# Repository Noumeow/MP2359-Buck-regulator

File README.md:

# MP2359-Buck-regulator
This is the first buck regulator I designed following the datasheet as correctly as I could without following any tutorial or anything
Here the voltage can be regulated more efficiently and 12V is stepped down to 3.3V
The enable pin has to have less than 6V for turning the chip on
The feedback resistors help in controlling the output to 3.3V
The A03401A p channel MOSFET works as a reverse polarity protection and better than the diode 1N4007 since the voltage drop in MOSFET is around 50-100mV while for the diode it is almost 0.7V.So the MOSFET is basically superior in terms of voltage drop,efficiency and heat dissipation

# Known Limitations and Future Improvements
The SW loop path with catch diode,inductor and capacitor needs to be as small as possible and clustered together.Even a few mm increase in trace introduce inductance causing voltage spike,electromagnetic interference and efficiency loss which needs to be improved in this design

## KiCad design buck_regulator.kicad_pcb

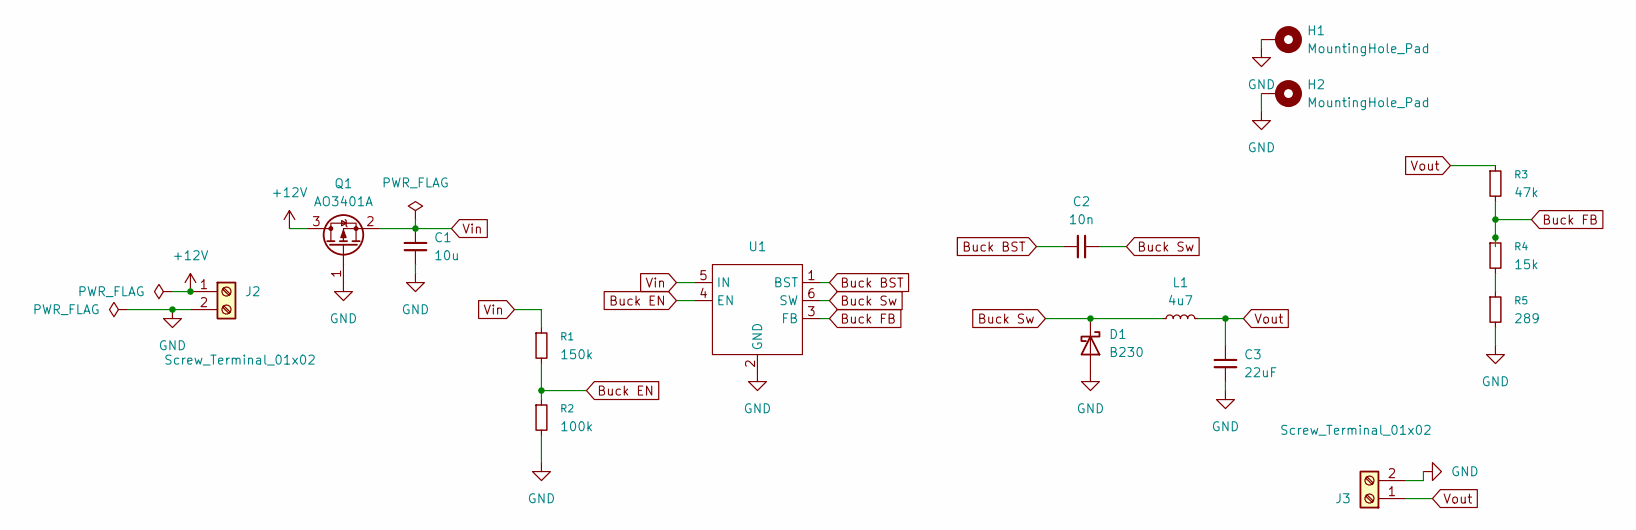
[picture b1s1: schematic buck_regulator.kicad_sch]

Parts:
C1: 10u; C_1206_3216Metric
C2: 10n; C_0805_2012Metric
C3: 22uF; C_1206_3216Metric
D1: B230; D_SMB
H1, H2: MountingHole_Pad; MountingHole_2.7mm_M2.5_Pad
J2, J3: Screw_Terminal_01x02; TerminalBlock_Phoenix_MKDS-1,5-2_1x02_P5.00mm_Horizontal
L1: 4u7; L_Sunlord_SWPA5020S
Q1: AO3401A; SOT-23
R1: 150k; R_0603_1608Metric
R2: 100k; R_0603_1608Metric
R3: 47k; R_0603_1608Metric
R4: 15k; R_0603_1608Metric
R5: 289; R_0603_1608Metric
U1: SOT-23-6

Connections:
+12V: J2.1, Q1.3 (D)
Buck BST: C2.1, U1.1 (BST)
Buck EN: R1.2, R2.1, U1.4 (EN)
Buck FB: R3.2, R4.1, U1.3 (FB)
Buck Sw: C2.2, D1.1 (K), L1.1, U1.6 (SW)
GND: C1.2, C3.1, D1.2 (A), H1.1 (1_1), H2.1 (1_1), J2.2, J3.2, Q1.1 (G), R2.2, R5.2, U1.2 (GND)
unnamed: R4.2, R5.1
Vin: C1.1, Q1.2 (S), R1.1, U1.5 (IN)
Vout: C3.2, J3.1, L1.2, R3.1

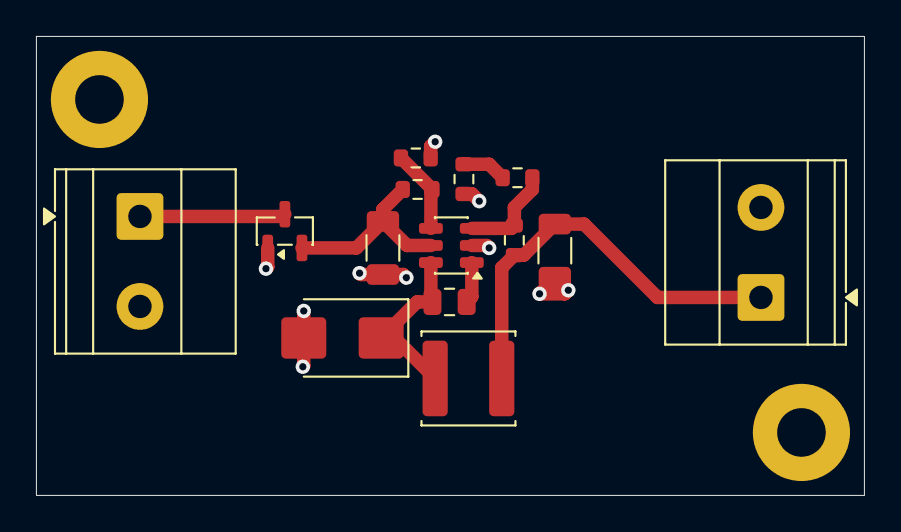
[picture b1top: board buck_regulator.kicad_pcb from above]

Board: 2 copper layers, 46.0 x 25.5 mm, 16 parts (0 on the bottom side), 9 nets.
